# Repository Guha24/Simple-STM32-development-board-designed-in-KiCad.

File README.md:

# STM32 Development Board PCB Design

This project is a simple STM32-based development board designed using KiCad for learning and practice purposes. The schematic was inspired by Phil’s Lab STM32 hardware design tutorial, while the PCB component placement and routing were implemented independently to gain practical understanding of PCB design workflows.

## Learning Objectives

* Understanding STM32 hardware design basics
* Practicing schematic capture and PCB routing
* Learning PCB layout considerations such as grounding, trace routing, and component placement
* Exploring embedded hardware development workflow

## Notes

This project was created for educational purposes to improve PCB design.

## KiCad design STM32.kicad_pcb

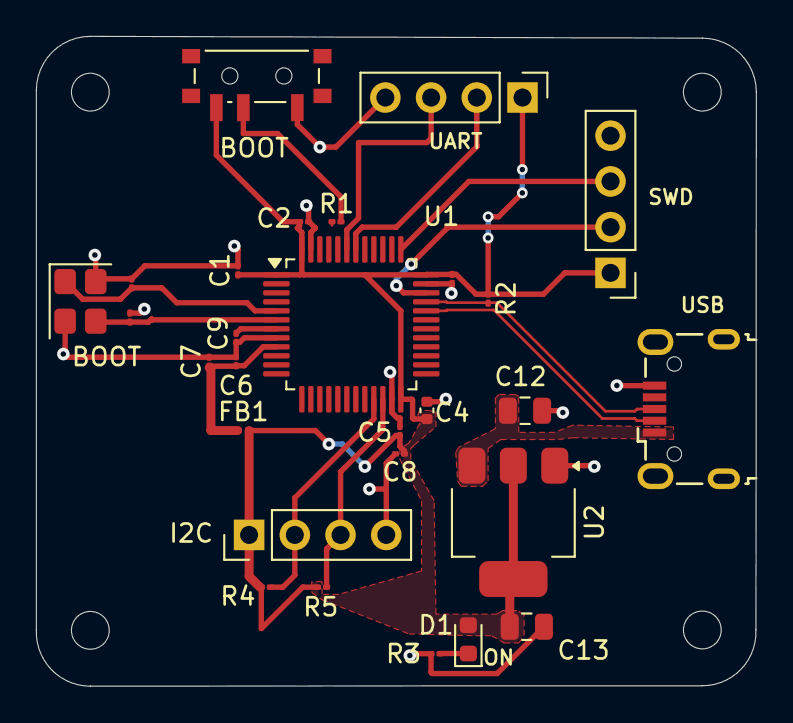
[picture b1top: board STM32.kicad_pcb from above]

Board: 4 copper layers, 40.0 x 36.1 mm, 32 parts (0 on the bottom side), 18 nets.

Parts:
BOOT: SW_SPDT; SW_SPDT_PCM12
BOOT#2: 16MHz; Crystal_SMD_3225-4Pin_3.2x2.5mm
C1, C2, C3, C5, C9: 100n; C_01005_0402Metric
C4: 10u; C_0402_1005Metric
C6: 10n; C_01005_0402Metric
C7, C8: 1u; C_01005_0402Metric
C10, C11: 10p; C_01005_0402Metric
C12, C13: 22u; C_0805_2012Metric
D1: RED; LED_0603_1608Metric
FB1: FerriteBead; L_0201_0603Metric
H1, H2, H3, H4: MountingHole_2.1mm
I2C: Conn_01x04_Pin; PinHeader_1x04_P2.54mm_Vertical
J1: USB_B_Micro; USB_Micro-B_Wuerth_629105150521
J2, J3: Conn_01x04_Pin; PinHeader_1x04_P2.54mm_Vertical
R1: 10k; R_01005_0402Metric
R2, R3, R4, R5: 1k5; R_01005_0402Metric
U1: STM32F103C8T6; LQFP-48_7x7mm_P0.5mm
U2: AMS1117-3.3; SOT-223-3_TabPin2

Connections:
+3.3V: BOOT.3 (C), C1.1, C2.1, C3.1, C4.1, C5.1, C8.1, C13.1, D1.2 (A), FB1.2, I2C.1, J2.1, J3.1, R2.1, R4.1, R5.1, U1.1 (VBAT), U1.24 (VDD), U1.36 (VDD), U1.48 (VDD), U2.2 (VO)
+3.3VA: C6.1, C7.1, FB1.1, U1.9 (VDDA)
/BOOT0: R1.1, U1.44 (BOOT0)
/HSC_IN: BOOT#2.1, C10.1, U1.5 (PD0)
/HSC_OUT: BOOT#2.3, C11.1, U1.6 (PD1)
/I2C2_SCL: I2C.2, R4.2, U1.21 (PB10)
/I2C2_SDA: I2C.3, R5.2, U1.22 (PB11)
/NRST: C9.1, U1.7 (NRST)
/SWCLK: J2.3, U1.37 (PA14)
/SWDIO: J2.2, U1.34 (PA13)
/SW_BOOT0: BOOT.2 (B), R1.2
/USART1_RX: J3.3, U1.43 (PB7)
/USART1_TX: J3.2, U1.42 (PB6)
/USB_D+: J1.3 (D+), R2.2, U1.33 (PA12)
/USB_D-: J1.2 (D-), U1.32 (PA11)
GND: BOOT.1 (A), BOOT#2.2 (G), BOOT#2.4 (G), C1.2, C2.2, C3.2, C4.2, C5.2, C6.2, C7.2, C8.2, C9.2, C10.2, C11.2, C12.2, C13.2, I2C.4, J1.5 (GND), J2.4, J3.4, R3.2, U1.8 (VSSA), U1.23 (VSS), U1.35 (VSS), U1.47 (VSS), U2.1 (GND)
unnamed: D1.1 (K), R3.1
VBUS: C12.1, J1.1 (VBUS), U2.3 (VI)

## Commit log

2026-05-25 Create Images
2026-05-25 Create 3D View
2026-05-25 Create test
2026-05-25 Rename Screenshot 2026-05-25 122829.png to PCB Layout
2026-05-25 Rename Screenshot 2026-05-25 122921.png to 3D_view.png
2026-05-25 Rename Screenshot 2026-05-25 122829.png to PCB_Layout.png
2026-05-25 Rename Screenshot 2026-05-25 123929.png to Schematic.png
2026-05-25 Create Gerbers folder
